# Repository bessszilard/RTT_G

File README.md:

# RTT_G
## The Autonomous Sign Detector and Object Tracker Robot

*Keywords: differential drive robot, real-time image processing, GUI, Arduino, PCB design, motor control.*

The project includes the construction of a robot with differential drive, itsʼ control mechanism and machine vision based guidance. The robot is controlled by an ATmega2560 microcontroller on an Arduino development board. Itsʼ structure also contains the following elements: sensor-electronics, two DC motors, two accumulators, one servo motor, vision system with active illumination and one Bluetooth module. A proprietary interface card connects the microcontroller with the sensors and the interveners.
The strategic level guidance is accomplished with an application running on PC based architecture. The PC and the robot communicate with each other via Bluetooth. The robot can work in two modes: first one is the manual control mode, the second one is the autonomous mode.
First program is the manually operated mode, in which the user can guide the robot using the PCʼs keyboard. The second program implements autonomous guidance. In this mode, PC controls the robot based on the result of processing a video feed from a mobile phone mounted onto the robot. Image processing is performed on the PC using Emgu CV which is based on the OpenCV libraries.

https://www.youtube.com/watch?v=aYvZUBr8wPQ

## Installing Arduino IDE
* [Windows install](https://www.arduino.cc/en/guide/windows)
* [Linux](https://www.arduino.cc/en/guide/linux)
* [MAC](https://www.dummies.com/computers/arduino/how-to-install-arduino-for-mac-os-x/)

## Arduino projects
* R_TTG_IMG_Proc_9_Serial - Robot is controlled with a Machine Vision program
* R_TTG_Timers_Encoder_test_PID_4 - Robot is controlled with keyboard

## License
MIT License

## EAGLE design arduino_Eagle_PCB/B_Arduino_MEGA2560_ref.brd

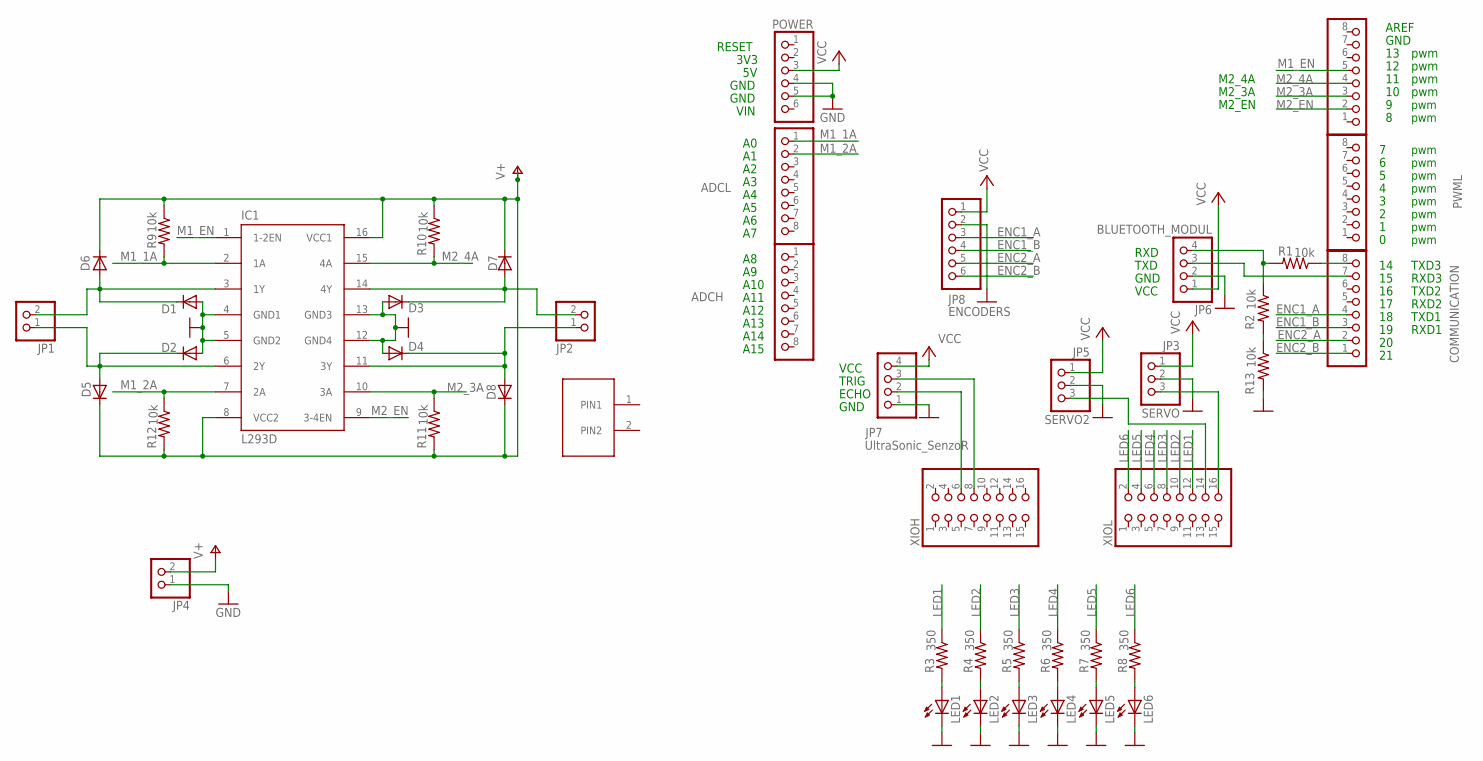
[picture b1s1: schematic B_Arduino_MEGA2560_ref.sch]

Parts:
ADCH: PINHD-1X8; 1X08
ADCL: PINHD-1X8; 1X08
COMMUNICATION: PINHD-1X8; 1X08
D1, D2, D3, D4, D5, D6, D7, D8: PMLL4150; SOD80C
IC1: L293D; DIL16
JP1, JP2, JP4: PINHD-1X2; 1X02
JP3: SERVO; 1X03
JP5: SERVO2; 1X03
JP6: BLUETOOTH_MODUL; 1X04
JP7: UltraSonic_SenzoR; 1X04
JP8: ENCODERS; 1X06
LED1, LED2, LED3, LED4, LED5, LED6: LED; SMARTLED-TTW
POWER: PINHD-1X6; 1X06
PWMH: PINHD-1X8; 1X08
PWML: PINHD-1X8; 1X08
R1, R2, R9, R10, R11, R12, R13: 10k; R0805
R3, R4, R5, R6, R7, R8: 350; R0805
U$1: FR_L_PNHD_2; FR_L_PN_HD-2
XIOH: PINHD-2X8; 2X08
XIOL: PINHD-2X8; 2X08

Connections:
ENC1_A: COMMUNICATION.4, JP8.3
ENC1_B: COMMUNICATION.3, JP8.4
ENC2_A: COMMUNICATION.2, JP8.5
ENC2_B: COMMUNICATION.1, JP8.6
GND: D1.A, D2.A, D3.A, D4.A, IC1.4 (GND1), IC1.5 (GND2), IC1.12 (GND4), IC1.13 (GND3), JP3.2, JP4.1, JP5.2, JP6.2, JP7.1, JP8.2, LED1.C@1 (C), LED2.C@1 (C), LED3.C@1 (C), LED4.C@1 (C), LED5.C@1 (C), LED6.C@1 (C), POWER.4, POWER.5, R13.2
LED1: R3.1, XIOL.12
LED2: R4.1, XIOL.10
LED3: R5.1, XIOL.8
LED4: R6.1, XIOL.6
LED5: R7.1, XIOL.4
LED6: R8.1, XIOL.2
M1_1A: ADCL.1, IC1.2 (1A), R9.2
M1_2A: ADCL.2, IC1.7 (2A), R12.1
M1_EN: IC1.1 (1-2EN), PWMH.5
M2_3A: IC1.10 (3A), PWMH.3, R11.1
M2_4A: IC1.15 (4A), PWMH.4, R10.2
M2_EN: IC1.9 (3-4EN), PWMH.2
unnamed: D1.C, D6.A, IC1.3 (1Y), JP1.2
unnamed: D2.C, D5.A, IC1.6 (2Y), JP1.1
unnamed: D3.C, D7.A, IC1.14 (4Y), JP2.2
unnamed: D4.C, D8.A, IC1.11 (3Y), JP2.1
unnamed: JP3.3, XIOL.16
unnamed: COMMUNICATION.7, JP6.3
unnamed: COMMUNICATION.8, R1.1
unnamed: JP6.4, R1.2, R2.1
unnamed: R2.2, R13.1
unnamed: JP7.3, XIOH.8
unnamed: JP7.2, XIOH.6
unnamed: LED1.A@1 (A), R3.2
unnamed: LED2.A@1 (A), R4.2
unnamed: LED3.A@1 (A), R5.2
unnamed: LED4.A@1 (A), R6.2
unnamed: LED5.A@1 (A), R7.2
unnamed: LED6.A@1 (A), R8.2
unnamed: JP5.3, XIOL.14
V+: D5.C, D6.C, D7.C, D8.C, IC1.8 (VCC2), IC1.16 (VCC1), JP4.2, R9.1, R10.1, R11.2, R12.2
VCC: JP3.1, JP5.1, JP6.1, JP7.4, JP8.1, POWER.3

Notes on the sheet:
pwm
GND
AREF
A10
A11
A12
A13
A14
A15
RESET
3V3
VIN
TXD3
RXD3
TXD2
RXD2
TXD1
RXD1
VCC
TXD
RXD
TRIG
ECHO
M2_EN
M2_4A
M2_3A

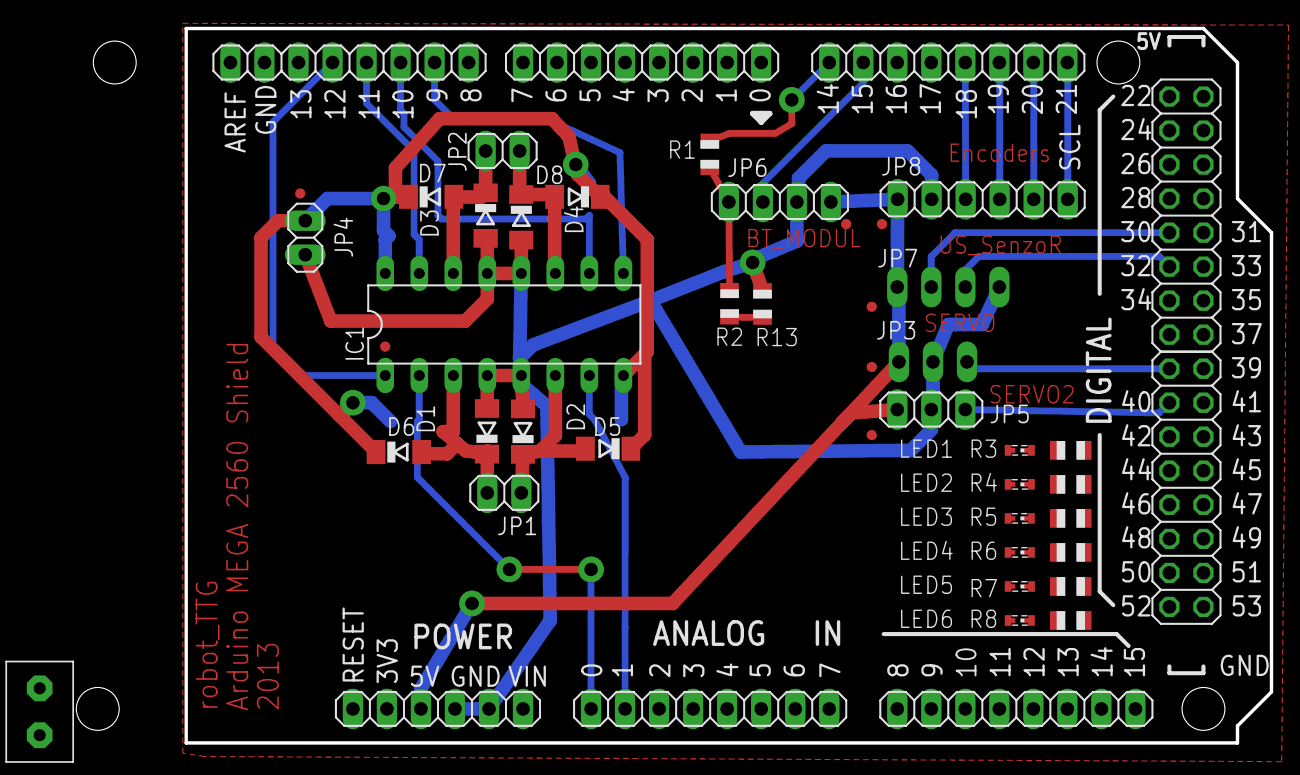
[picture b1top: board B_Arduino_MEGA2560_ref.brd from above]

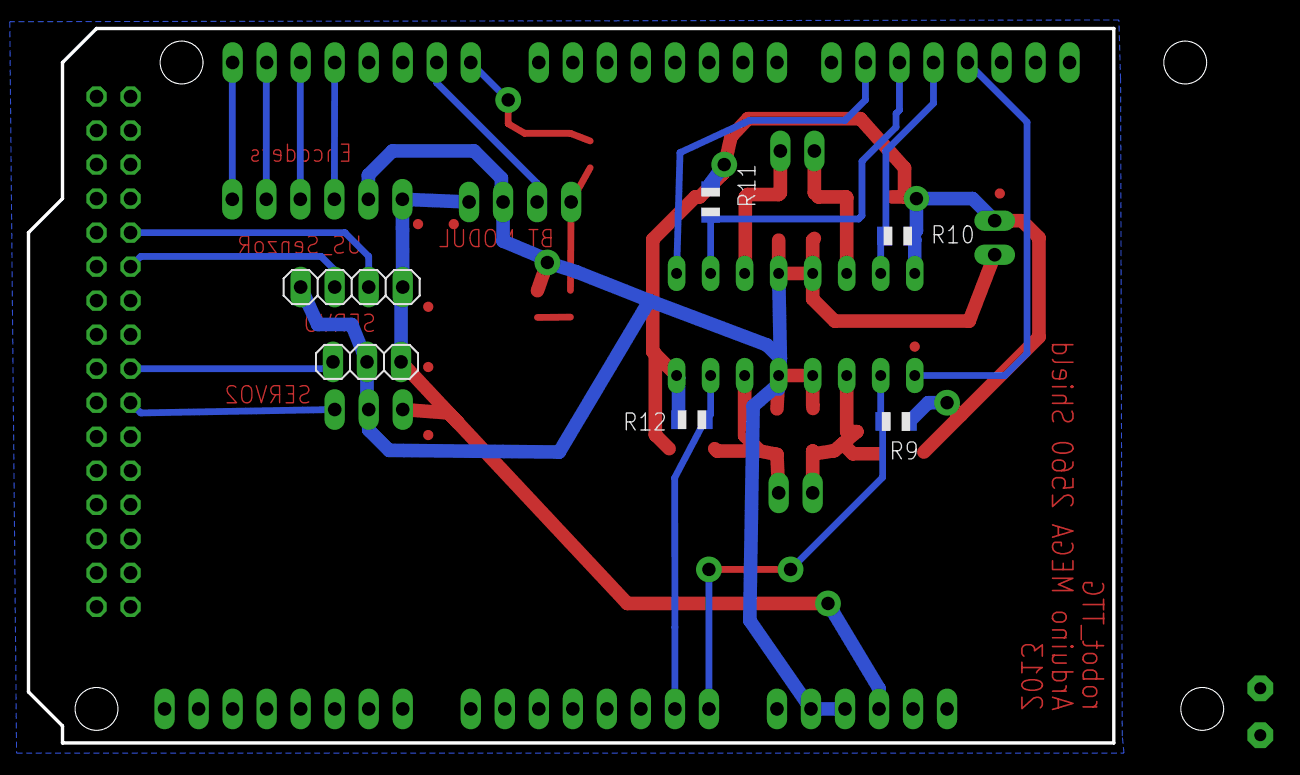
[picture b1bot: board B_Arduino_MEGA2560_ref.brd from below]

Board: 2 copper layers, 81.0 x 53.3 mm, 45 parts (6 on the bottom side), 37 nets.

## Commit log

2019-04-26 Added the basic descrioption of a project
2019-04-26 Arduino projects added
    Robot is controlled by Machine Vision algorithm in R_TTG_IM_Proc_9 .
    Robot is controlled manualle via Keyboard in R_TTG_Timers_Encoder_test_PID_4 project
    These projects were created in 2014
2019-04-27 PCB and pictures added
    Added Eagle files and pictures
2019-04-30 Closed loop control picture is updated
    Bug fixed: The closed loop picture text changed to English from Hungarian
    Picture is updated, ready for the readme
2019-04-30 Added install description and additional info
    Update: Descriptions and closed loop added to README.md file
    Added Installation description, Closed loop control picture, Arduino project descriptions, and License description.
